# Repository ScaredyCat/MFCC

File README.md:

# MFCC
My first Clock Controller - My Corona Virus lockdown project (2020 - just in case there's another outbreak)

I was furloughed during 2020 and legally wasn't allowed to work for my employer so I took the time to try and learn somthing new. That turned out to be this project, learning how to use Kicad and how to build a radio-time enabled clock. Most of the things I've built in the past don't survive for too long, the Arduino is invariably repurposed for the next project and so on. This time it was different.

# Before we start

Most of this is really new to me. I've never designed a circuit board of any real complexity before this and I wouldn't particularly trust that my electronics knowledge is any use at all.

I've made some modifications to both the MSFDecoder library and the JQ6500 library so they are included here for completeness.

# Board

I used a DIYMORE Arduino Leonardo Clone for this project they are half the price of a Genuine Arduino Leonardo and have pins broken out to header pins in addition to the standard headers. The also have GND and 5v broken out for each pin and additional header pins for serial and i2c. This is really the sort of connectivity that I think should be on the genuine boards, but I guess they have reasons for not doing it.

The "motherboard" is really a deliberately oversized Arduino shield but it removes a lot of the wires and provides a stable platform for all the components. I appreciate my soldering leaves a lot to be desired. I used pin headers quite a bit for my connections just for convenience - they turned out to be inconvenient when wires kept popping out of them. Many of the connections do not get populated as they are for other options.

# Modules

The design is fairly modular and uses off the shelf modules to provide additional features. Prices at time of purchase (May-Oct 2020)

 - I2C:  LCD Display, Non volatile memory (EEPROM), DS3231
 - SPI:  7 Segment displays

 Major parts:

- 2 x JQ6500 for audio - if you don't want audio or only want chimes or only want tick-tock then it's up to you. Approx cost from aliexpress is £1/unit

- 2 x 7 segment display boards 0.56" 8 displays on a board Approx cost from aliexpress is £1.40/unit dependant on colour selected.

- 1 x LCD display with backpack Approx cost from aliexpress is £5/unit

- 1 x DS3231 module Approx cost from aliexpress is £0.90/unit

- 1 x buck converter for power Approx cost from aliexpress is £1/unit

- 1 x MSF receiver (CANADUINO) £11.18 + shipping (£5.40) - cost more than the price of getting the "motherboard" made, takes a long time to arrive. No other suppliers found as alternative. This can be swapped out for the DCF77 board if you want to use the DCF77 time signal (code changes required, same price
though)

- LED strip of WS2812B I picked up a 1 metre strip with 60 leds on it for £4.25 from aliexpress.

- Various header pins and headers these work out at about £0.15 each from aliexpress but I just got a box of them from an Amazon seller.

- An old (or new) quartz clock mechanism.

- PCB cost￡9.85 + ￡5.22 shipping that's for the minimum quantity of 5 boards.

You can get these parts at places like amazon for slightly inflated prices but without the 2 week wait - sometimes prices are the same so shop around.

Without access to something like [JLCPCB](https://jlcpcb.com/) [No, they didn't sponsor me] none of this would have really happened - it would have been another rats nest of wires project that survived for a limited time before repurposing the Arudino. Access to services like this make a huge difference to people starting out and the existance of software like [kICad](https://kicad-pcb.org/) makes the process of design to physical board simple. How many newbies would fork out £100's for pcb design software if they were just trying something out? KiCad is free and it's awesome and major component suppliers support the library format too.

# Issues

The biggest issue you are going to face is getting a good signal from Anthorn (Cumbria) - (or your location for WWVB, JJY). My workspace/office has lots of electrical equipment in it which interferes with the signal. Nothing during the day (the sun buggers up the signal) but better at night in with the receiver near a window. The antenna should be at 90 degrees to the expected signal path for best reception. Rotating it 90 degrees can change the signal level by 20-30dB. Initially my results were great but they have got steadily worse with a sync taking place maybe twice a fortnight if I'm lucky.

Having tweaked the MSFDecoder to cut down on noise thigs have got much better, not a lot of syncing during the day but occasioanal ones and quite a lot of syncing at night/early morning. I'm getting multiple syncs a day.

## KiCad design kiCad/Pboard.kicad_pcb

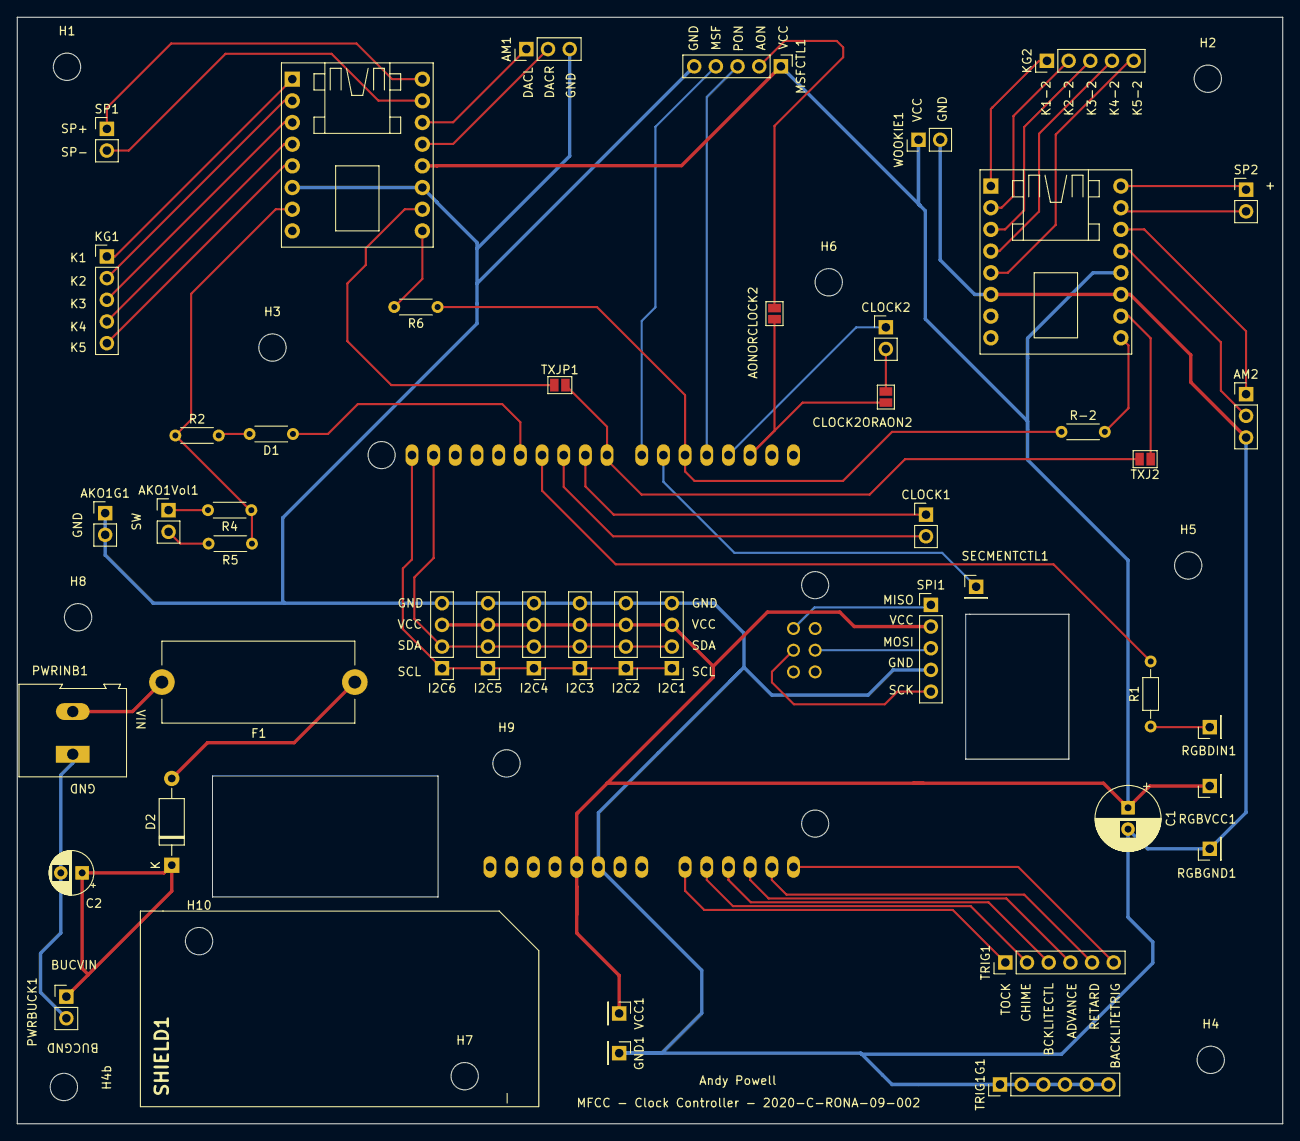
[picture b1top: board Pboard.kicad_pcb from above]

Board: 2 copper layers, 148.3 x 129.7 mm, 58 parts (0 on the bottom side), 57 nets.

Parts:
AKO1G1, AKO1Vol1: Conn_01x02; PinHeader_1x02_P2.54mm_Vertical
AM1, AM2: Amp; PinHeader_1x03_P2.54mm_Vertical
AONORCLOCK2: SolderJumper_2_Open; SolderJumper-2_P1.3mm_Open_Pad1.0x1.5mm
C1: 1000uF; CP_Radial_D7.5mm_P2.50mm
C2: 4.7; CP_Radial_D5.0mm_P2.50mm
CLOCK1, CLOCK2: Conn_01x02; PinHeader_1x02_P2.54mm_Vertical
CLOCK2ORAON2: SolderJumper_2_Open; SolderJumper-2_P1.3mm_Open_Pad1.0x1.5mm
D1: D; R_Axial_DIN0204_L3.6mm_D1.6mm_P5.08mm_Horizontal
D2: D; D_A-405_P10.16mm_Horizontal
F1: 3A; Fuseholder_Cylinder-5x20mm_Stelvio-Kontek_PTF78_Horizontal_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
GND1: Conn_01x01; PinHeader_1x01_P2.54mm_Vertical
H1, H2, H3, H4, H4b, H5, H6, H7, H8, H9, H10: MountingHole; MountingHole_3.2mm_M3
I2C1, I2C2, I2C3, I2C4, I2C5, I2C6: Conn_01x04; PinHeader_1x04_P2.54mm_Vertical
KG1, KG2: Keys; PinHeader_1x05_P2.54mm_Vertical
MSFCTL1: Conn_01x05; PinHeader_1x05_P2.54mm_Vertical
PWRBUCK1: Conn_01x02; PinHeader_1x02_P2.54mm_Vertical
PWRINB1: Screw_Terminal_01x02; TerminalBlock_Altech_AK300-2_P5.00mm
R1: 330; R_Axial_DIN0204_L3.6mm_D1.6mm_P7.62mm_Horizontal
R2: 100K; R_Axial_DIN0204_L3.6mm_D1.6mm_P5.08mm_Horizontal
R4: 6.2k; R_Axial_DIN0204_L3.6mm_D1.6mm_P5.08mm_Horizontal
R5: 3.3K; R_Axial_DIN0204_L3.6mm_D1.6mm_P5.08mm_Horizontal
R6: R1K; R_Axial_DIN0204_L3.6mm_D1.6mm_P5.08mm_Horizontal
R-2: R1K; R_Axial_DIN0204_L3.6mm_D1.6mm_P5.08mm_Horizontal
RGBDIN1: Conn_01x01; PinHeader_1x01_P2.54mm_Vertical
RGBGND1: Conn_01x01; PinHeader_1x01_P2.54mm_Vertical
RGBVCC1: Conn_01x01; PinHeader_1x01_P2.54mm_Vertical
SECMENTCTL1: Conn_01x01; PinHeader_1x01_P2.54mm_Vertical
SHIELD1: ARDUINO_SHIELD
SP1, SP2: Speaker; PinHeader_1x02_P2.54mm_Vertical
SPI1: Conn_01x05; PinHeader_1x05_P2.54mm_Vertical
TRIG1, TRIG1G1: Conn_01x06; PinHeader_1x06_P2.54mm_Vertical
TXJ2: SolderJumper_2_Open; SolderJumper-2_P1.3mm_Open_Pad1.0x1.5mm
TXJP1: SolderJumper_2_Open; SolderJumper-2_P1.3mm_Open_Pad1.0x1.5mm
U1, U2: JQ6500-16P_Module; JQ6500_2x8_P2.54mm
VCC1: Conn_01x01; PinHeader_1x01_P2.54mm_Vertical
WOOKIE1: Conn_01x02; PinHeader_1x02_P2.54mm_Vertical

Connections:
ADKEY: R2.1, R4.1, R5.1, U2.7
ADVANCE: SHIELD1.AD3, TRIG1.4
AON: AONORCLOCK2.2, MSFCTL1.2
BCKLITETRIG: SHIELD1.AD5, TRIG1.6
CHIMES: SHIELD1.AD1, TRIG1.2
CLOCKA: CLOCK1.1, SHIELD1.9
CLOCKB: CLOCK1.2, SHIELD1.10
CLOCKC: CLOCK2.1, SHIELD1.3
CLOCKD: CLOCK2.2, CLOCK2ORAON2.2
DACL: AM1.1, U2.14
DACL-2: AM2.1, U1.14
DACR: AM1.2, U2.13
DACR-2: AM2.2, U1.13
GND: AKO1G1.1, AKO1G1.2, AM1.3, AM2.3, C1.2, GND1.1, I2C1.4, I2C2.4, I2C3.4, I2C4.4, I2C5.4, I2C6.4, MSFCTL1.5, RGBGND1.1, SHIELD1.GND1, SPI1.4, TRIG1G1.1, TRIG1G1.2, TRIG1G1.3, TRIG1G1.4, TRIG1G1.5, TRIG1G1.6, U1.6, U1.11, U2.6, U2.11, WOOKIE1.2
INGND: C2.2, PWRBUCK1.2, PWRINB1.1
JQRX: R6.1, R-2.1, SHIELD1.5
JQTICKTOCK: D1.1, SHIELD1.12
JQTX: SHIELD1.8, TXJ2.2, TXJP1.2
K1: KG1.1, U2.1
K1-2: KG2.1, U1.1
K2: KG1.2, U2.2
K2-2: KG2.2, U1.2
K3: KG1.3, U2.3
K3-2: KG2.3, U1.3
K4: KG1.4, U2.4
K4-2: KG2.4, U1.4
K5: KG1.5, U2.5
K5-2: KG2.5, U1.5
LCDBACKLIGHT: SHIELD1.AD2, TRIG1.3
LEDDATA: R1.2, SHIELD1.11
MISO-NR: SHIELD1.SP1, SPI1.1
MOSI-NR: SHIELD1.SP4, SPI1.3
MSF: MSFCTL1.4, SHIELD1.7
unnamed: AKO1Vol1.1, R4.2
unnamed: AKO1Vol1.2, R5.2
unnamed: AONORCLOCK2.1, CLOCK2ORAON2.1, SHIELD1.2
unnamed: D1.2, R2.2
unnamed: D2.2, F1.1
unnamed: F1.2, PWRINB1.2
unnamed: R1.1, RGBDIN1.1
PBVCC: C2.1, D2.1, PWRBUCK1.1
PON: MSFCTL1.3, SHIELD1.4
RETARD: SHIELD1.AD4, TRIG1.5
RX: R6.2, U2.9
RX-2: R-2.2, U1.9
SCK-NR: SHIELD1.SP3, SPI1.5
SCL: I2C1.1, I2C2.1, I2C3.1, I2C4.1, I2C5.1, I2C6.1, SHIELD1.SCL
SDA: I2C1.2, I2C2.2, I2C3.2, I2C4.2, I2C5.2, I2C6.2, SHIELD1.SDA
SEGMENT: SECMENTCTL1.1, SHIELD1.6
SPK+: SP1.1, U2.16
SPK+-2: SP2.1, U1.16
SPK-: SP1.2, U2.15
SPK--2: SP2.2, U1.15
TICKTOCK: SHIELD1.AD0, TRIG1.1
TX: TXJP1.1, U2.10
TX-2: TXJ2.1, U1.10
VCC: C1.1, I2C1.3, I2C2.3, I2C3.3, I2C4.3, I2C5.3, I2C6.3, MSFCTL1.1, RGBVCC1.1, SHIELD1.5V, SPI1.2, U1.12, U2.12, VCC1.1, WOOKIE1.1

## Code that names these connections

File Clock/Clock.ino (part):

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    6   MAX7219_CS        - Drive 7 segment led arrays via SPI
    7   INTERRUPT 4       - Interrupt for MSF receiver
    8   JQ6500            - Software serial port for JQ6500 #2 to trigger chimes
    9   CLOCKA            - Drive pin for quartz clock requires 2 pins
    10  CLOCKB            - sending alternating pulses, 30ms pulse for 120ms
    11  LED_PIN           - For control of LED strip for notification LEDs.
    12  AUTOTOCK          - Hardware loop to JQ6500 #1 for repeated Tick-Tock.
    A0  TICKTOCKSWITCH    - Enable or disable tick-tock sound from JQ6500 #1
    A1  CHIMESWITCH       - Enable or disable 1/4 hour and hourly chimes from JQ6500 #2
    A2  BACKLIGHT_PIN     - Allows us to turn the LCD backlight on or off. Any value < 128 = Off
    A3  ADVANCE_PIN       - momentary switch turns advance on.
    A4  RETARD_PIN        - Momentary switch to retard pulses.
    A5  BACKLIGHT_TRIGGER - Force backlight on or off


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    they all take a pule to move a second's worth.
*/

const int CLOCKA = 9;         // Main analog clock pins
const int CLOCKB = 10;        // for alternate pulses.

/*
    Switches to disable or enable sounds and the backlight
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const int TICKTOCKSWITCH = A0;
const int CHIMESWITCH = A1;
const int BACKLIGHT_PIN = A2;
const int ADVANCE_PIN = A3;
const int RETARD_PIN = A4;
const int BACKLIGHT_TRIGGER = A5;
const int PON = 4;


/*
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   MSF library needs an interrupt. This depends on the device being used and how many
   interrupts you have

   PON is a pin to allow powering the board on and off but in this instance power is
   'plentiful' so not required and we need the pins anyway.


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
bool bstChangeForwardNow = false;
bool bstChangeBackwardNow = false;
const int bstTicks = 3600 + 720;  // 1 hour plus the time taken to advance an hour
const int bstRetards = 3600;
bool bstChanged = false;
bool bst = false;
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#define   LED_MIRROR 11
#define   LED_SYNC_TODAY 10

#define   TICKTOCK 9
#define   CHIMING 8

#define   LED_BSTSOON 7
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
void setup() {

  pinMode(PON, OUTPUT);
  digitalWrite(PON, LOW);

  pinMode(TICKTOCKSWITCH, INPUT_PULLUP);
  pinMode(CHIMESWITCH, INPUT_PULLUP);
  pinMode(ADVANCE_PIN, INPUT_PULLUP);
  pinMode(RETARD_PIN, INPUT_PULLUP);
  pinMode(BACKLIGHT_TRIGGER, INPUT_PULLUP);
  pinMode(twoSecondPulse, OUTPUT);

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 //while (!Serial);
 

  MSF.init(aInputPin, aInterrupt);

  Clock.begin();

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  strip.show();            // Turn OFF all pixels ASAP
  strip.setBrightness(MAX_BRIGHTNESS); // Set BRIGHTNESS to about 1/5 (max = 255)

  pinMode(CLOCKA, OUTPUT);
  pinMode(CLOCKB, OUTPUT);
  digitalWrite(CLOCKA, LOW);
  digitalWrite(CLOCKB, LOW);

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      }
    }

    MSF.TimeAvailable = 0;
  } else {

    // doing this makes me vomit a little each time I see it.
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  soundTickTock = !digitalRead(TICKTOCKSWITCH);
  soundChime = !digitalRead(CHIMESWITCH);
  backlightState = digitalRead(BACKLIGHT_TRIGGER);
  advance = !digitalRead(ADVANCE_PIN);
  retard = !digitalRead(RETARD_PIN);

  if (advance) {
    //advance = digitalRead(ADVANCE_PIN);
    lcdindicatorLED(LED_ADVANCE, advance);
    indicatorLED(LED_ADVANCE, GREEN, OFF, advance);
    advanceCount = 5;
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
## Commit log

2020-10-14 Tidy up
2020-10-14 Modified libraries used
    Libraries with modifications.
    JQ6500 doesn't wait for completion of audio, we just want it triggered and then forgotten about.
    I've added BST, BST Change and LED mirror to MSFDecoder.
2020-10-14 KiCad data and code commit
    Need to tidy up the code quite a bit. Trying to be good and document stuff.
2020-10-14 Move files
    Peobably help if I put the files in the right place.
2020-10-14 it not is
2020-10-14 spelling
2020-10-14 Attribution
2020-10-14 "FIx" time loss
    Increase the minimum PULSE_IGNORE_WIDTH to 80 to try and remove noise
2020-10-14 Test chime removal
    Remove test chime at 10 past the hour..
2020-10-15 Removed big issue text
    Refining code to ignore short pulses, removing getting temperature from DS3231 every second tweaking display options to use saved time rather than using second() etc re-reading the time - thanks to "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
2020-10-15 Update Clock.ino
    Remove timezone related code, not required. Use frozen time for displays. Remove test (commented out code)
2020-10-15 Update Clock.ino
    freeze time
2020-10-15 Update Clock.ino
    Forgot retarding when BST changes
2020-10-15 Update Clock.ino
    comment
2020-10-17 Fix displayed time bug
    Freezing the second caused unexpected corruption of data of lcd and 7 segment displays.
2020-10-17 Days of week start at 1
    Days of week don't start at 0 as in linux. 1 is Sunday here.
2020-10-19 Use frozenTime
2020-10-20 update issues
